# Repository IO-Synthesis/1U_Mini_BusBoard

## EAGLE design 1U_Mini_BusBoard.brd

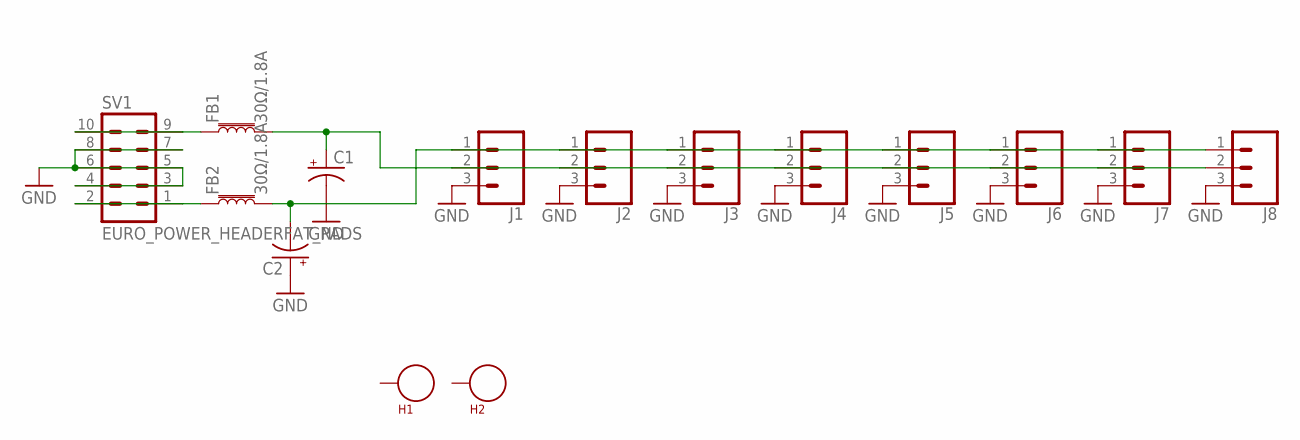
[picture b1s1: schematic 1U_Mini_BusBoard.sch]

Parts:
C1, C2: CPOL-USC; PANASONIC_C
FB1, FB2: 30Ω/1.8A; 0603
H1, H2: SEW_HOLE; SIMPLE_HOLE
J1, J2, J3, J4, J5, J6, J7, J8: CONN_031X03_NO_SILK; 1X03_NO_SILK
SV1: EURO_POWER_HEADERFAT_PADS; EURO_PWR_HEADER_FAT

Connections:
GND: C1.-, C2.+, J1.3, J2.3, J3.3, J4.3, J5.3, J6.3, J7.3, J8.3, SV1.3, SV1.4, SV1.5, SV1.6, SV1.7, SV1.8
unnamed: FB1.1, SV1.9, SV1.10
unnamed: FB2.1, SV1.1, SV1.2
unnamed: C1.+, FB1.2, J1.2, J2.2, J3.2, J4.2, J5.2, J6.2, J7.2, J8.2
unnamed: C2.-, FB2.2, J1.1, J2.1, J3.1, J4.1, J5.1, J6.1, J7.1, J8.1

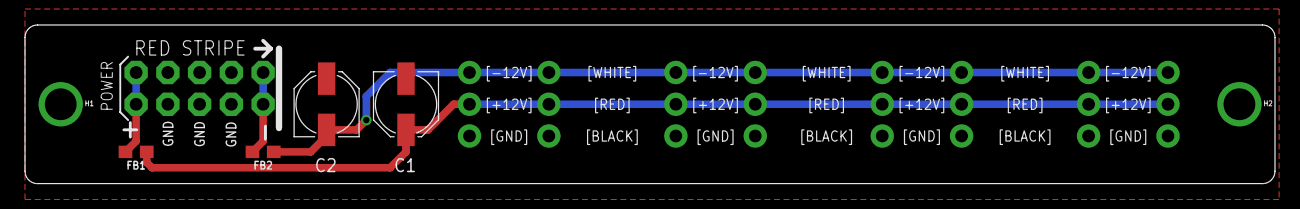
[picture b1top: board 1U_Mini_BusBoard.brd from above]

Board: 2 copper layers, 100.0 x 12.7 mm, 15 parts (0 on the bottom side), 5 nets.

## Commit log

2017-01-09 :circus_tent: Added .gitattributes & .gitignore files
2017-02-09 Set theme jekyll-theme-hacker
2017-03-18 1U_Mini_BusBoard

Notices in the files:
parts and their libraries:
SparkFun-Coils: Licensing: Creative Commons ShareAlike 4.0 International - https://creativecommons.org/licenses/by-sa/4.0
